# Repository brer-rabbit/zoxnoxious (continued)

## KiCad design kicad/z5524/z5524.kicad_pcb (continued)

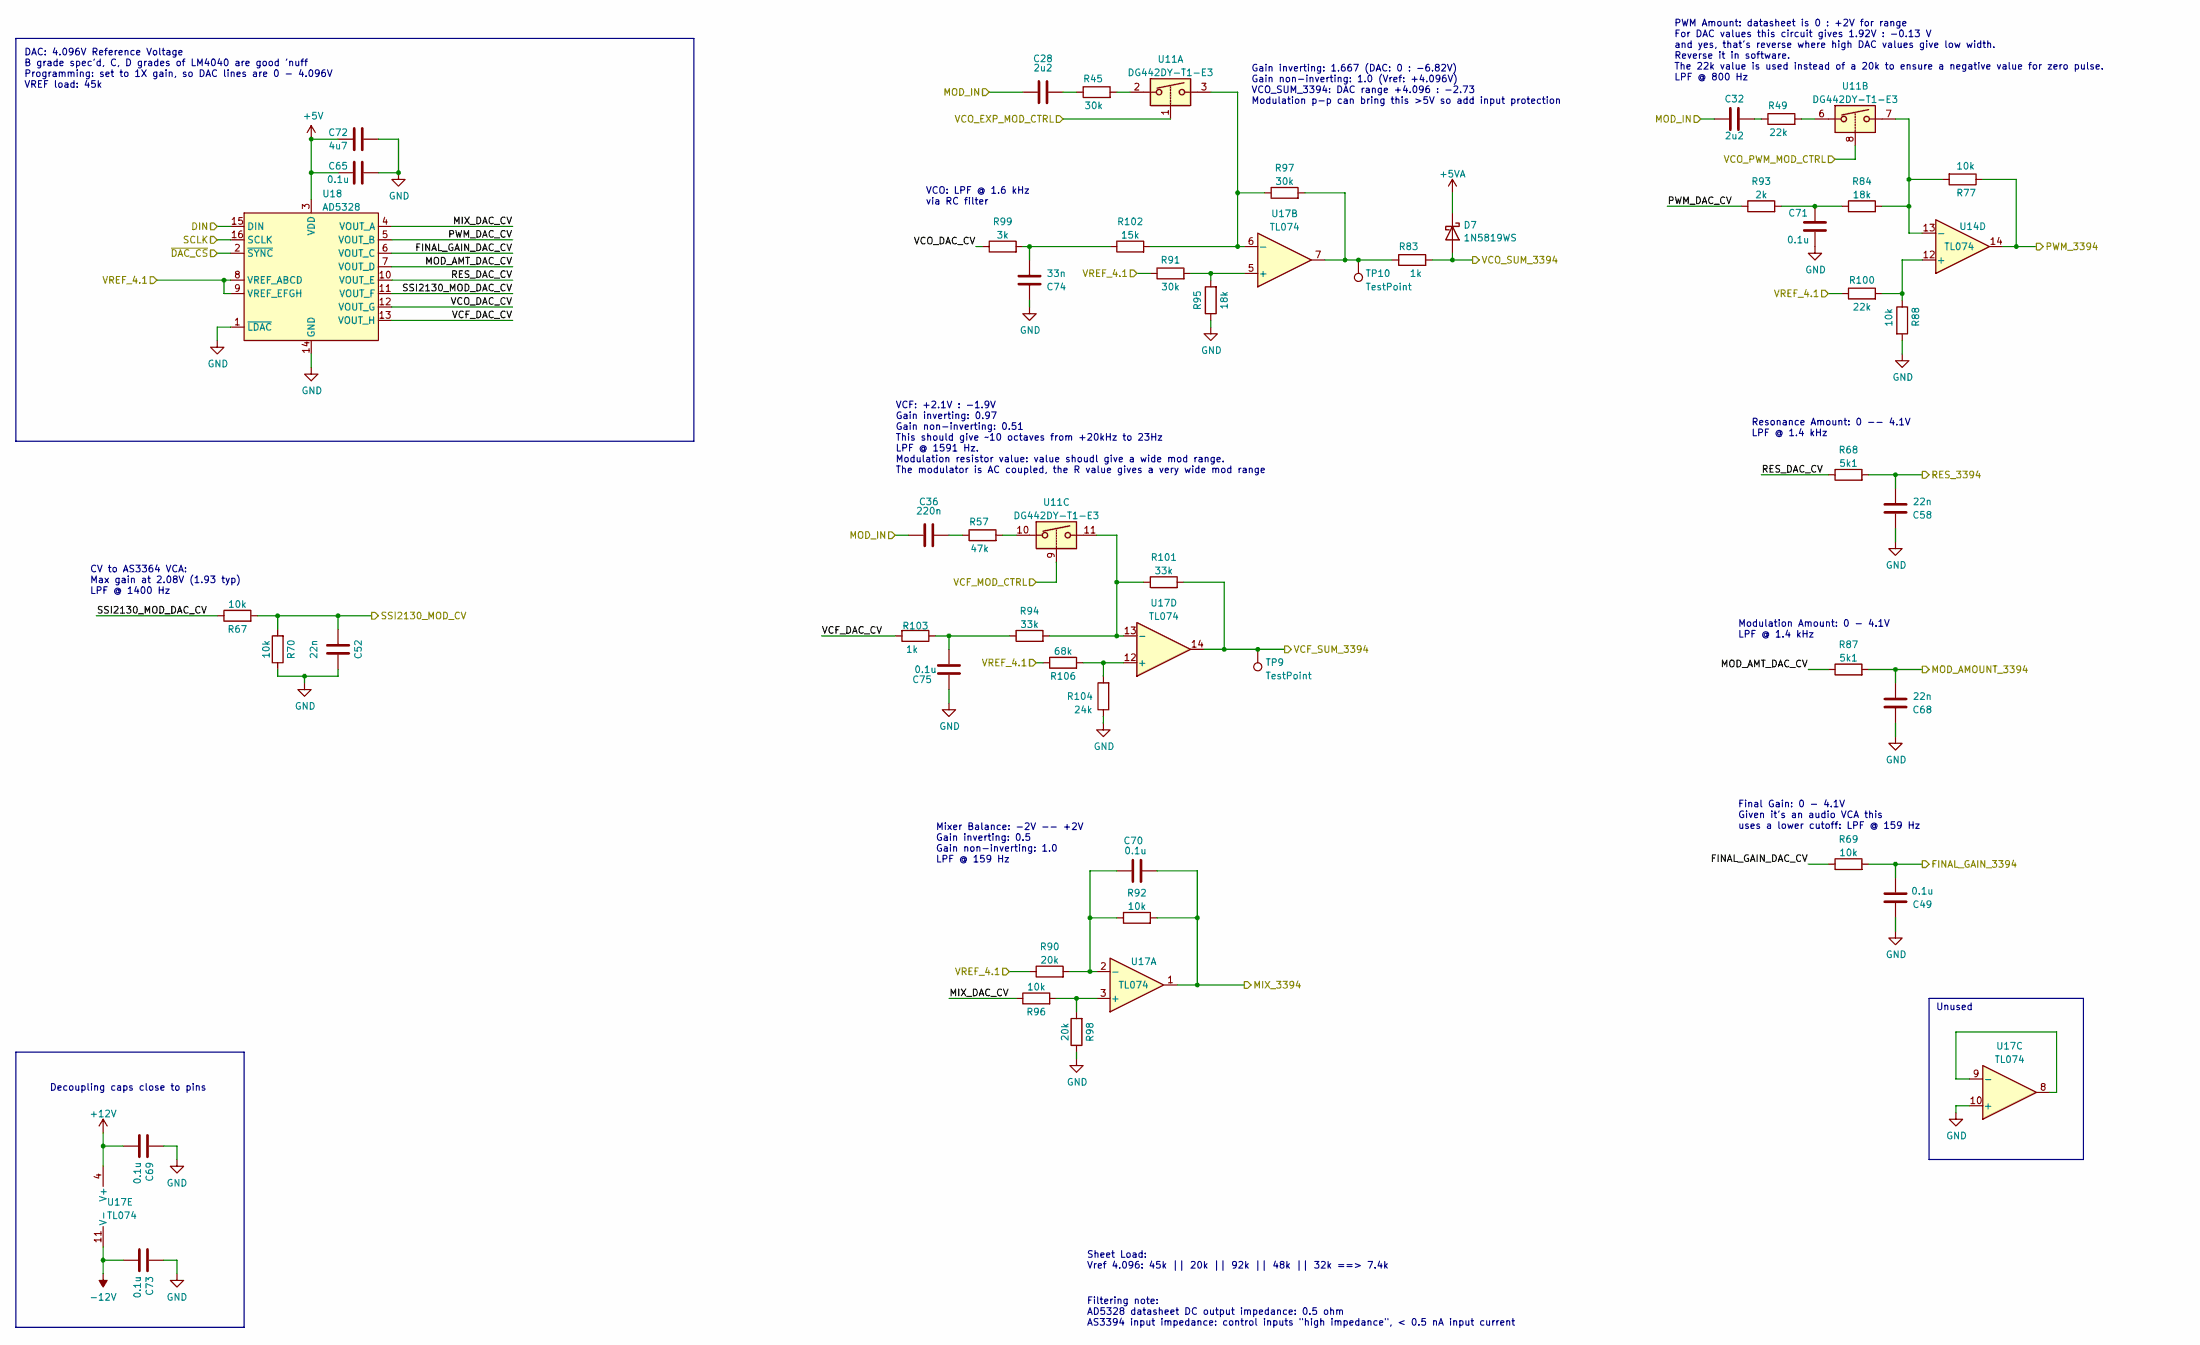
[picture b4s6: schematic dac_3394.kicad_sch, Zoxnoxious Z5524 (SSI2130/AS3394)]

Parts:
C28, C32: 2u2; C_0603_1608Metric; LCSC C23630
C36: 220n; C_0603_1608Metric; LCSC C21120
C49, C65, C69, C70, C71, C73, C75: 0.1u; C_0603_1608Metric; LCSC C14663
C52, C58, C68: 22n; C_0603_1608Metric; LCSC C21122
C72: 4u7; C_0603_1608Metric; LCSC C19666
C74: 33n; C_0603_1608Metric; LCSC C21117
D7: 1N5819WS; D_SOD-323; LCSC C191023
R45, R91, R97: 30k; R_0603_1608Metric; LCSC C22984
R49, R100: 22k; R_0603_1608Metric; LCSC C31850
R57: 47k; R_0603_1608Metric; LCSC C25819
R67, R69, R70, R77, R88, R92, R96: 10k; R_0603_1608Metric; LCSC C25804
R68, R87: 5k1; R_0603_1608Metric; LCSC C23186
R83, R103: 1k; R_0603_1608Metric; LCSC C21190
R84, R95: 18k; R_0603_1608Metric; LCSC C25810
R90, R98: 20k; R_0603_1608Metric; LCSC C4184
R93: 2k; R_0603_1608Metric; LCSC C22975
R94, R101: 33k; R_0603_1608Metric; LCSC C4216
R99: 3k; R_0603_1608Metric; LCSC C4211
R102: 15k; R_0603_1608Metric; LCSC C22809
R104: 24k; R_0603_1608Metric; LCSC C23352
R106: 68k; R_0603_1608Metric; LCSC C23231
TP9, TP10: TestPoint; TestPoint_Pad_1.5x1.5mm
U11: DG442DY-T1-E3; SOIC-16_3.9x9.9mm_P1.27mm; LCSC C2673321
U14, U17: TL074; TSSOP-14_4.4x5mm_P0.65mm; LCSC C96507
U18: AD5328; TSSOP-16_4.4x5mm_P0.65mm; LCSC C29162

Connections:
+5V: C65.1, C72.1, U18.3 (VDD); also elsewhere on the board
+5VA: D7.1 (K); also elsewhere on the board
+12V: C69.2, U17.4 (V+); also elsewhere on the board
-12V: C73.2, U17.11 (V-); also elsewhere on the board
/AS3394/FINAL_GAIN_CV: C49.1, R69.2; also elsewhere on the board
/AS3394/MIX_CV: C70.2, R92.2, U17.1; also elsewhere on the board
/AS3394/MOD_AMOUNT_CV: C68.1, R87.2; also elsewhere on the board
/AS3394/PWM_SUM: R77.1, U14.14; also elsewhere on the board
/AS3394/RES_CV: C58.1, R68.2; also elsewhere on the board
/AS3394/VCF_SUM: R101.2, TP9.1, U17.14; also elsewhere on the board
/AS3394/VCO_SUM: D7.2 (A), R83.2; also elsewhere on the board
/DAC 3394/FINAL_GAIN_DAC_CV: R69.1, U18.6 (VOUT_C)
/DAC 3394/MIX_DAC_CV: R96.1, U18.4 (VOUT_A)
/DAC 3394/MOD_AMT_DAC_CV: R87.1, U18.7 (VOUT_D)
/DAC 3394/PWM_DAC_CV: R93.1, U18.5 (VOUT_B)
/DAC 3394/RES_DAC_CV: R68.1, U18.10 (VOUT_E)
/DAC 3394/SSI2130_MOD_DAC_CV: R67.1, U18.11 (VOUT_F)
/DAC 3394/VCF_DAC_CV: R103.2, U18.13 (VOUT_H)
/DAC 3394/VCO_DAC_CV: R99.1, U18.12 (VOUT_G)
/PWM3394_MOD_CTRL: U11.8; also elsewhere on the board
/SPI_CLK: U18.16 (SCLK); also elsewhere on the board
/SPI_CS0: U18.2 (~SYNC); also elsewhere on the board
/SPI_MOSI: U18.15 (DIN); also elsewhere on the board
/SSI2130_MOD: C28.1, C32.1, C36.1; also elsewhere on the board
/SSI2130_MOD_CV: C52.2, R67.2, R70.2; also elsewhere on the board
/VCF3394_MOD_CTRL: U11.9; also elsewhere on the board
/VCO3394_EXP_MOD_CTRL: U11.1; also elsewhere on the board
/VREF_4.096: R90.1, R91.1, R100.1, R106.1, U18.8 (VREF_ABCD), U18.9 (VREF_EFGH); also elsewhere on the board
GND: C49.2, C52.1, C58.2, C65.2, C68.2, C69.1, C71.1, C72.2, C73.1, C74.2, C75.2, R70.1, R88.2, R95.1, R98.1, R104.1, U17.10 (+), U18.1 (~LDAC), U18.14 (GND); also elsewhere on the board
unnamed: C28.2, R45.1
unnamed: C32.2, R49.1
unnamed: C36.2, R57.1
unnamed: C71.2, R84.1, R93.2
unnamed: C74.1, R99.2, R102.1
unnamed: C75.1, R94.1, R103.1
unnamed: R45.2, U11.2
unnamed: R49.2, U11.6
unnamed: R57.2, U11.10
unnamed: R83.1, R97.2, TP10.1, U17.7
unnamed: R88.1, R100.2, U14.12 (+)
unnamed: R77.2, R84.2, U11.7, U14.13 (-)
unnamed: R96.2, R98.2, U17.3 (+)
unnamed: C70.1, R90.2, R92.1, U17.2 (-)
unnamed: R91.2, R95.2, U17.5 (+)
unnamed: R97.1, R102.2, U11.3, U17.6 (-)
unnamed: U17.8, U17.9 (-)
unnamed: R104.2, R106.2, U17.12 (+)
unnamed: R94.2, R101.1, U11.11, U17.13 (-)

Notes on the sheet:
PWM Amount: datasheet is 0 : +2V for range For DAC values this circuit gives 1.92V : -0.13 V and yes, that's reverse where high DAC values give low width. Reverse it in software. The 22k value is used instead of a 20k to ensure a negative value for zero pulse. LPF @ 800 Hz
VCO: LPF @ 1.6 kHz via RC filter
VCF: +2.1V : -1.9V Gain inverting: 0.97 Gain non-inverting: 0.51 This should give ~10 octaves from +20kHz to 23Hz LPF @ 1591 Hz. Modulation resistor value: value shoudl give a wide mod range. The modulator is AC coupled, the R value gives a very wide mod range
Resonance Amount: 0 -- 4.1V LPF @ 1.4 kHz
Unused
Sheet Load: Vref 4.096: 45k || 20k || 92k || 48k || 32k ==> 7.4k
Mixer Balance: -2V -- +2V Gain inverting: 0.5 Gain non-inverting: 1.0 LPF @ 159 Hz
Modulation Amount: 0 - 4.1V LPF @ 1.4 kHz
Filtering note: AD5328 datasheet DC output impedance: 0.5 ohm AS3394 input impedance: control inputs "high impedance", < 0.5 nA input current
Final Gain: 0 - 4.1V Given it's an audio VCA this uses a lower cutoff: LPF @ 159 Hz
DAC: 4.096V Reference Voltage B grade spec'd, C, D grades of LM4040 are good 'nuff Programming: set to 1X gain, so DAC lines are 0 - 4.096V VREF load: 45k
CV to AS3364 VCA: Max gain at 2.08V (1.93 typ) LPF @ 1400 Hz
Decoupling caps close to pins
Gain inverting: 1.667 (DAC: 0 : -6.82V) Gain non-inverting: 1.0 (Vref: +4.096V) VCO_SUM_3394: DAC range +4.096 : -2.73 Modulation p-p can bring this >5V so add input protection

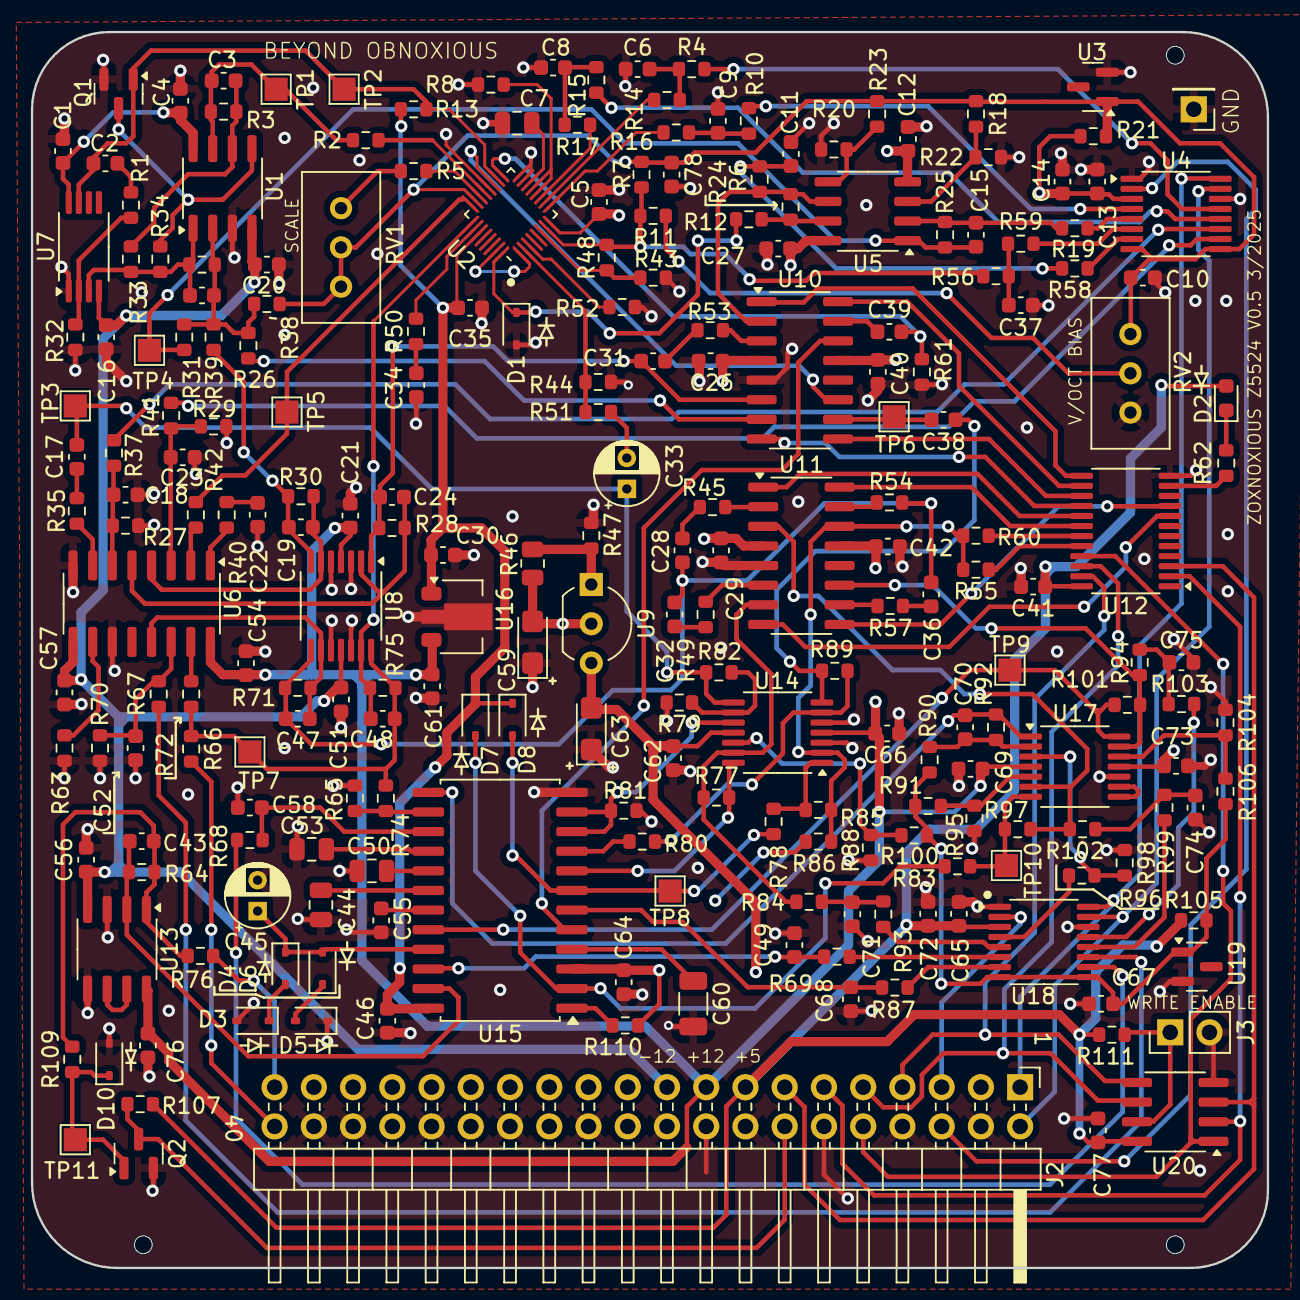
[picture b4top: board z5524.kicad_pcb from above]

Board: 4 copper layers, 80.0 x 80.0 mm, 233 parts (0 on the bottom side), 164 nets.

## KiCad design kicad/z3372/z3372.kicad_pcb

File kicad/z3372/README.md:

# Z3372 Voltage Controlled Filter & Noise Source

The Z3372 Analog Signal Processor utilized Alfa Rpar's AS3372 VCF/VCA.  It also contains a white noise source which can be run through the filter.  Some interseting modulation options are present, along with a stereo output.

# Block Diagram

# Resources

[Datasheet](datasheet_z3372.pdf)

[KiCanvas](https://kicanvas.org/?github=https%3A%2F%2Fgithub.com%2Fbrer-rabbit%2Fzoxnoxious%2Ftree%2Fmain%2Fkicad%2Fz3372)

# Demo

(old!) YouTube Demo

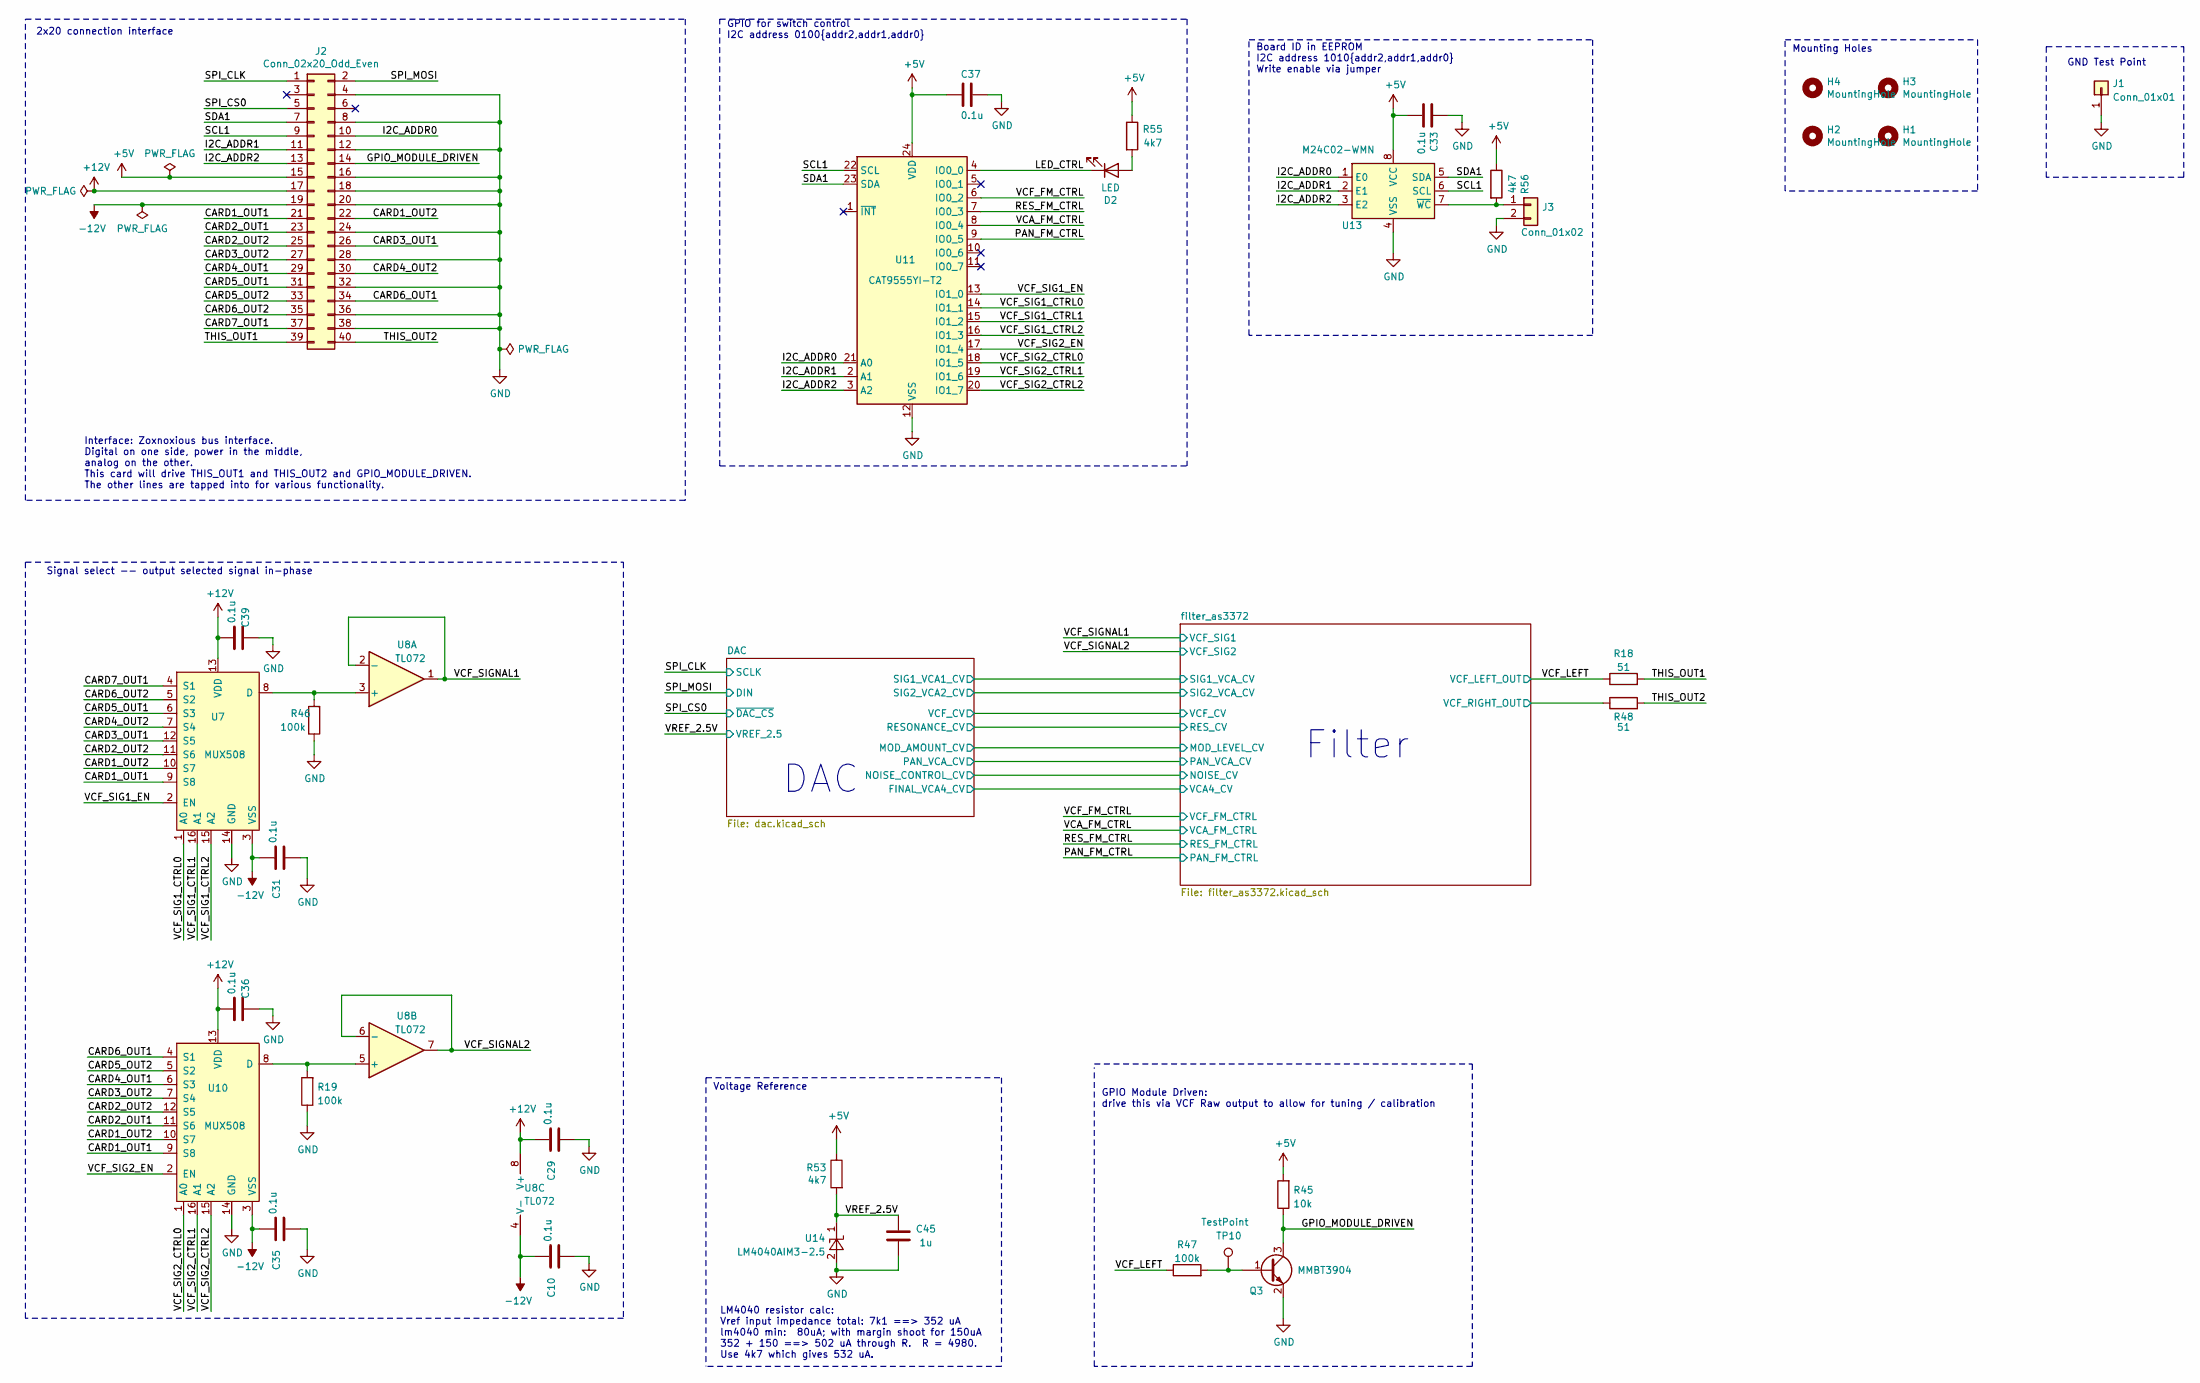
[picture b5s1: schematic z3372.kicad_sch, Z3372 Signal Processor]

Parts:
C10, C29, C31, C33, C35, C36, C37, C39: 0.1u; C_0603_1608Metric; LCSC C14663
C45: 1u; C_0805_2012Metric; LCSC C28323
D2: LED; LED_0603_1608Metric; LCSC C2286
H1, H2, H3, H4: MountingHole; MountingHole_3.2mm_M3
J1: Conn_01x01; PinHeader_1x01_P2.54mm_Vertical
J2: Conn_02x20_Odd_Even; PinHeader_2x20_P2.54mm_Horizontal
J3: Conn_01x02; PinHeader_1x02_P2.54mm_Vertical
Q3: MMBT3904; SOT-23; LCSC C20526
R18, R48: 51; R_0603_1608Metric; LCSC C23197
R19, R46, R47: 100k; R_0603_1608Metric; LCSC C25803
R45: 10k; R_0603_1608Metric; LCSC C25804
R53, R55, R56: 4k7; R_0603_1608Metric; LCSC C23162
TP10: TestPoint; TestPoint_Pad_2.0x2.0mm
U7, U10: MUX508; SOIC-16_3.9x9.9mm_P1.27mm; LCSC C2673104
U8: TL072; SOIC-8_3.9x4.9mm_P1.27mm; LCSC C6961
U11: CAT9555YI-T2; TSSOP-24_4.4x7.8mm_P0.65mm; LCSC C83265
U13: M24C02-WMN; SOIC-8_3.9x4.9mm_P1.27mm; LCSC C7562
U14: LM4040AIM3-2.5; SOT-23; LCSC C460725

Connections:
+5V: C33.2, C37.2, J2.15, R45.2, R53.1, R55.1, R56.1, U11.24 (VDD), U13.8 (VCC); also elsewhere on the board
+12V: C29.2, C36.2, C39.2, J2.17, U7.13 (VDD), U8.8 (V+), U10.13 (VDD); also elsewhere on the board
-12V: C10.2, C31.2, C35.2, J2.19, U7.3 (VSS), U8.4 (V-), U10.3 (VSS); also elsewhere on the board
/CARD1_OUT1: J2.21, U7.9 (S8), U10.9 (S8)
/CARD1_OUT2: J2.22, U7.10 (S7), U10.10 (S7)
/CARD2_OUT1: J2.23, U10.11 (S6)
/CARD2_OUT2: J2.25, U7.11 (S6), U10.12 (S5)
/CARD3_OUT1: J2.26, U7.12 (S5)
/CARD3_OUT2: J2.27, U10.7 (S4)
/CARD4_OUT1: J2.29, U10.6 (S3)
/CARD4_OUT2: J2.30, U7.7 (S4)
/CARD5_OUT1: J2.31, U7.6 (S3)
/CARD5_OUT2: J2.33, U10.5 (S2)
/CARD6_OUT1: J2.34, U10.4 (S1)
/CARD6_OUT2: J2.35, U7.5 (S2)
/CARD7_OUT1: J2.37, U7.4 (S1)
/GPIO_MODULE_DRIVEN: J2.14, Q3.3 (C), R45.1
/I2C_ADDR0: J2.10, U11.21 (A0), U13.1 (E0)
/I2C_ADDR1: J2.11, U11.2 (A1), U13.2 (E1)
/I2C_ADDR2: J2.13, U11.3 (A2), U13.3 (E2)
/LED_CTRL: D2.1 (K), U11.4 (IO0_0)
/PAN_FM_CTRL: U11.9 (IO0_5); also elsewhere on the board
/RES_FM_CTRL: U11.7 (IO0_3); also elsewhere on the board
/SCL1: J2.9, U11.22 (SCL), U13.6 (SCL)
/SDA1: J2.7, U11.23 (SDA), U13.5 (SDA)
/SPI_CLK: J2.1; also elsewhere on the board
/SPI_CS0: J2.5; also elsewhere on the board
/SPI_MOSI: J2.2; also elsewhere on the board
/THIS_OUT1: J2.39, R18.2
/THIS_OUT2: J2.40, R48.2
/VCA_FM_CTRL: U11.8 (IO0_4); also elsewhere on the board
/VCF_FM_CTRL: U11.6 (IO0_2); also elsewhere on the board
/VCF_LEFT: R18.1, R47.1; also elsewhere on the board
/VCF_SIG1_CTRL0: U7.1 (A0), U11.14 (IO1_1)
/VCF_SIG1_CTRL1: U7.16 (A1), U11.15 (IO1_2)
/VCF_SIG1_CTRL2: U7.15 (A2), U11.16 (IO1_3)
/VCF_SIG1_EN: U7.2 (EN), U11.13 (IO1_0)
/VCF_SIG2_CTRL0: U10.1 (A0), U11.18 (IO1_5)
/VCF_SIG2_CTRL1: U10.16 (A1), U11.19 (IO1_6)
/VCF_SIG2_CTRL2: U10.15 (A2), U11.20 (IO1_7)
/VCF_SIG2_EN: U10.2 (EN), U11.17 (IO1_4)
/VCF_SIGNAL1: U8.1, U8.2 (-); also elsewhere on the board
/VCF_SIGNAL2: U8.6 (-), U8.7; also elsewhere on the board
/VREF_2.5V: C45.1, R53.2, U14.1 (K); also elsewhere on the board
/filter_as3372/VCF_RIGHT_OUT: R48.1; also elsewhere on the board
GND: C10.1, C29.1, C31.1, C33.1, C35.1, C36.1, C37.1, C39.1, C45.2, J1.1, J2.4, J2.8, J2.12, J2.16, J2.18, J2.20, J2.24, J2.28, J2.32, J2.36, J2.38, J3.2, Q3.2 (E), R19.1, R46.1, U7.14 (GND), U10.14 (GND), U11.12 (VSS), U13.4 (VSS), U14.2 (A); also elsewhere on the board
unnamed: D2.2 (A), R55.2
unnamed: J3.1, R56.2, U13.7 (~WC)
unnamed: Q3.1 (B), R47.2, TP10.1
unnamed: R46.2, U7.8 (D), U8.3 (+)
unnamed: R19.2, U8.5 (+), U10.8 (D)

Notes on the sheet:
Filter
Signal select -- output selected signal in-phase
Voltage Reference
2x20 connection interface
GPIO Module Driven: drive this via VCF Raw output to allow for tuning / calibration
GPIO for switch control I2C address 0100{addr2,addr1,addr0}
Mounting Holes
LM4040 resistor calc: Vref input impedance total: 7k1 ==> 352 uA lm4040 min: 80uA; with margin shoot for 150uA 352 + 150 ==> 502 uA through R. R = 4980. Use 4k7 which gives 532 uA.
GND Test Point
Board ID in EEPROM I2C address 1010{addr2,addr1,addr0} Write enable via jumper
Interface: Zoxnoxious bus interface. Digital on one side, power in the middle, analog on the other. This card will drive THIS_OUT1 and THIS_OUT2 and GPIO_MODULE_DRIVEN. The other lines are tapped into for various functionality.
DAC

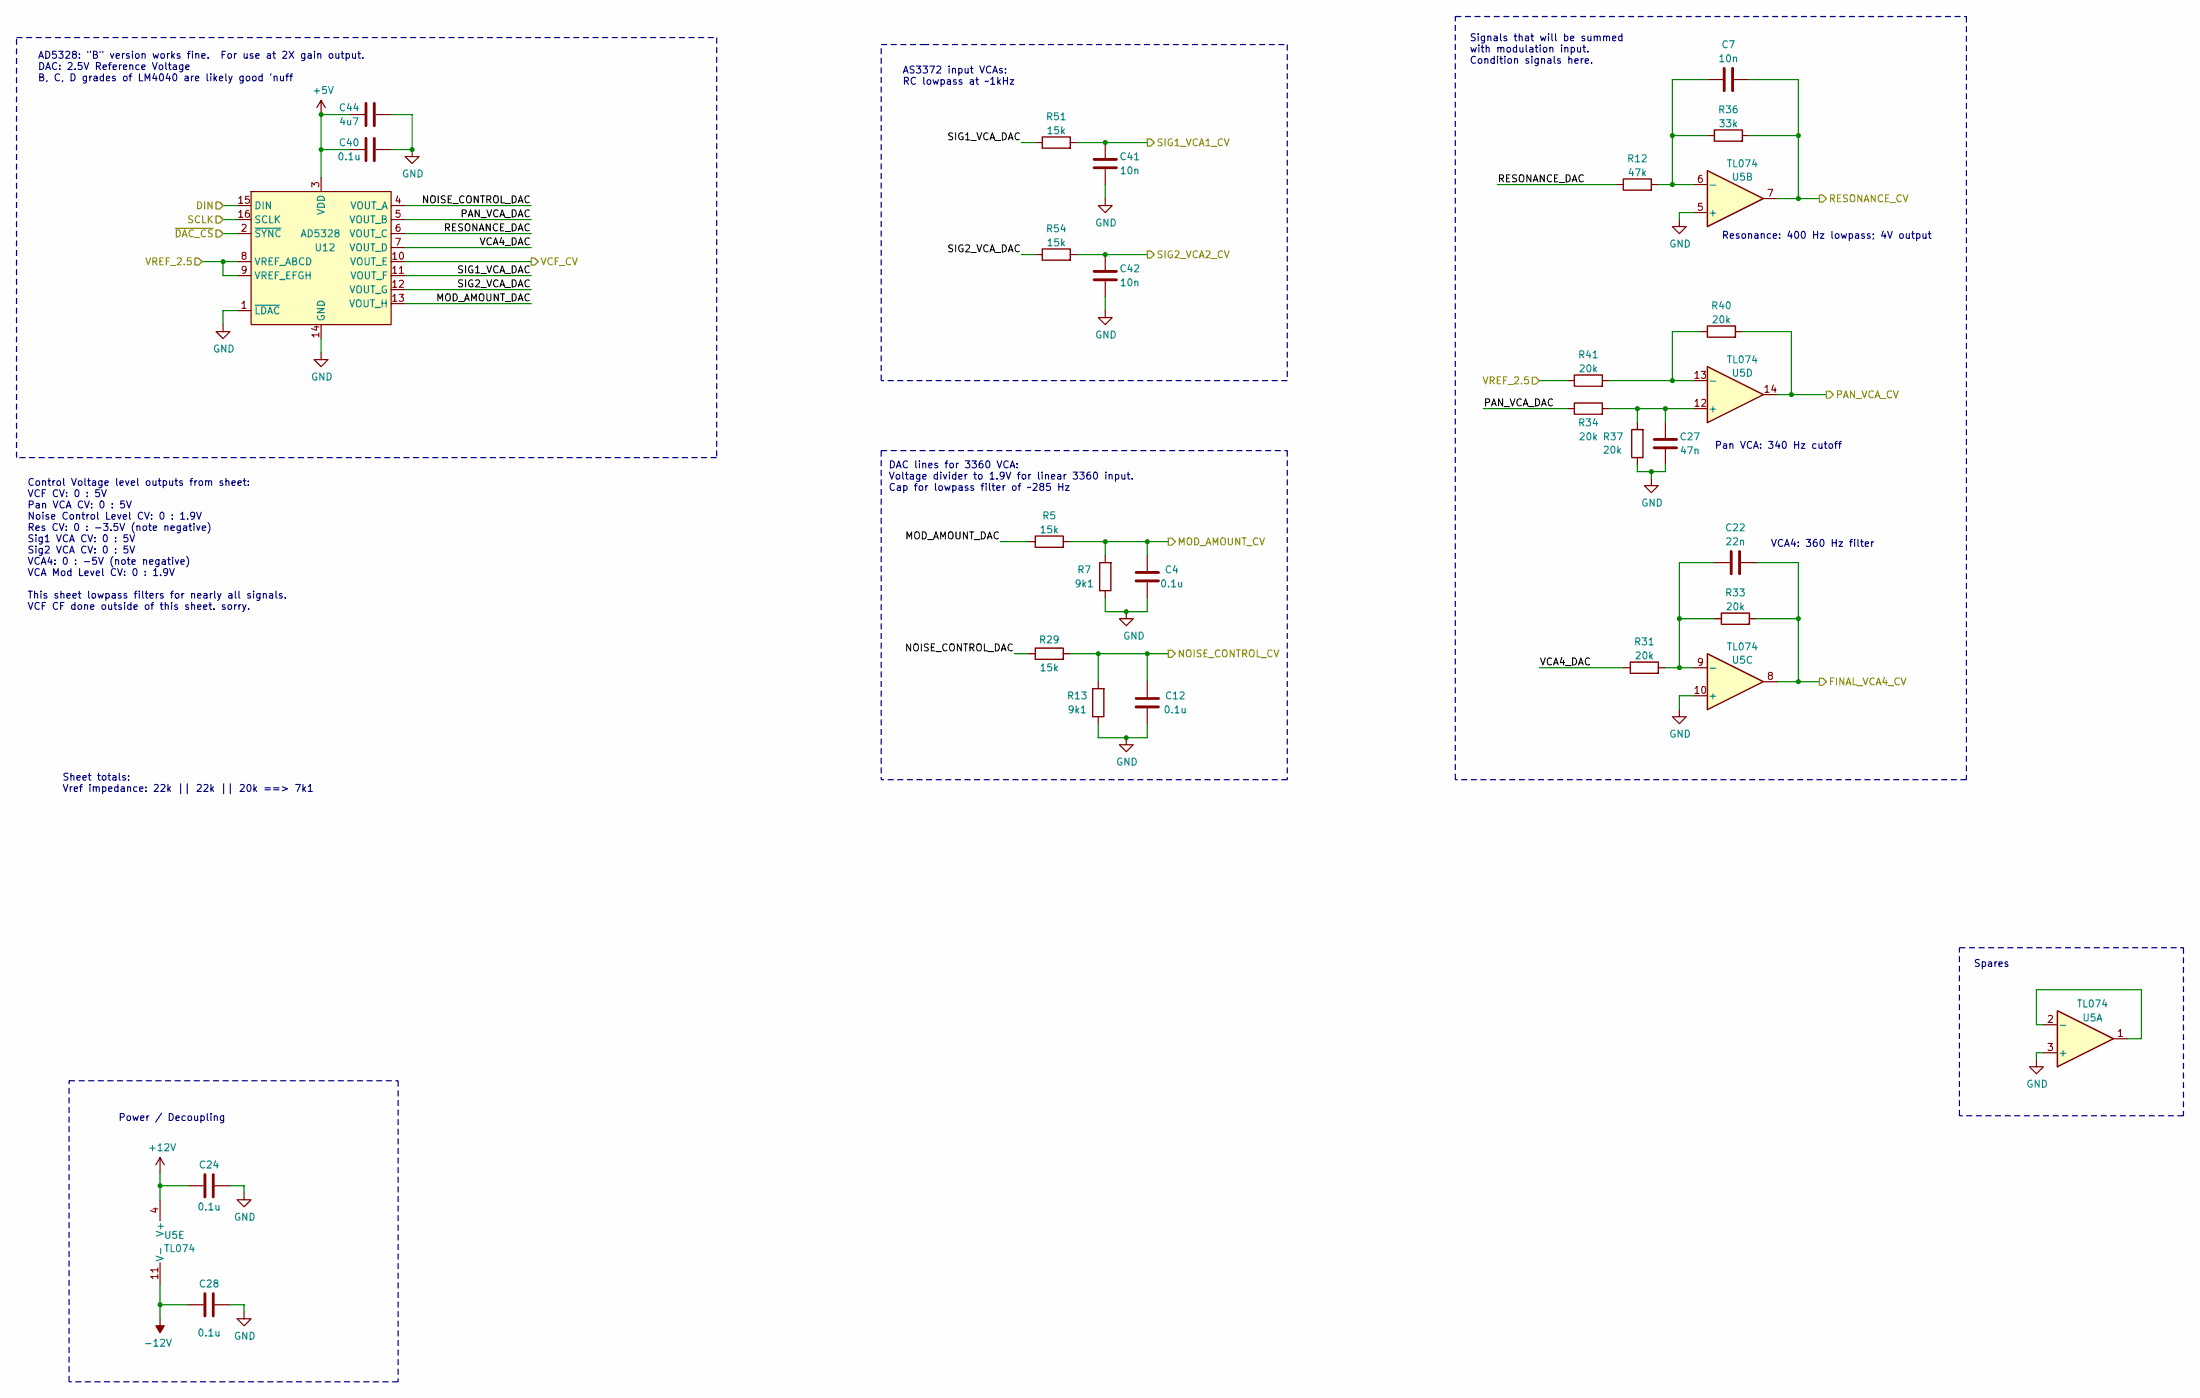
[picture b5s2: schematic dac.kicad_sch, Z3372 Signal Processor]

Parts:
C4, C12, C24, C28, C40: 0.1u; C_0603_1608Metric; LCSC C14663
C7, C41, C42: 10n; C_0603_1608Metric; LCSC C57112
C22: 22n; C_0603_1608Metric; LCSC C21122
C27: 47n; C_0603_1608Metric; LCSC C1622
C44: 4u7; C_0805_2012Metric; LCSC C1779
R5, R29, R51, R54: 15k; R_0603_1608Metric; LCSC C22809
R7, R13: 9k1; R_0603_1608Metric; LCSC C23260
R12: 47k; R_0603_1608Metric; LCSC C25819
R31, R33, R34, R37, R40, R41: 20k; R_0603_1608Metric; LCSC C4184
R36: 33k; R_0603_1608Metric; LCSC C4216
U5: TL074; TSSOP-14_4.4x5mm_P0.65mm; LCSC C96507
U12: AD5328; TSSOP-16_4.4x5mm_P0.65mm; LCSC C29162

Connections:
+5V: C40.1, C44.1, U12.3 (VDD); also elsewhere on the board
+12V: C24.1, U5.4 (V+); also elsewhere on the board
-12V: C28.1, U5.11 (V-); also elsewhere on the board
/DAC/FINAL_VCA4_CV: C22.2, R33.2, U5.8; also elsewhere on the board
/DAC/MOD_AMOUNT_CV: C4.1, R5.2, R7.2; also elsewhere on the board
/DAC/MOD_AMOUNT_DAC: R5.1, U12.13 (VOUT_H)
/DAC/NOISE_CONTROL_CV: C12.1, R13.2, R29.2; also elsewhere on the board
/DAC/NOISE_CONTROL_DAC: R29.1, U12.4 (VOUT_A)
/DAC/PAN_VCA_CV: R40.2, U5.14; also elsewhere on the board
/DAC/PAN_VCA_DAC: R34.1, U12.5 (VOUT_B)
/DAC/RESONANCE_CV: C7.2, R36.2, U5.7; also elsewhere on the board
/DAC/RESONANCE_DAC: R12.1, U12.6 (VOUT_C)
/DAC/SIG1_VCA1_CV: C41.1, R51.2; also elsewhere on the board
/DAC/SIG1_VCA_DAC: R51.1, U12.11 (VOUT_F)
/DAC/SIG2_VCA2_CV: C42.1, R54.2; also elsewhere on the board
/DAC/SIG2_VCA_DAC: R54.1, U12.12 (VOUT_G)
/DAC/VCA4_DAC: R31.1, U12.7 (VOUT_D)
/DAC/VCF_CV: U12.10 (VOUT_E); also elsewhere on the board
/SPI_CLK: U12.16 (SCLK); also elsewhere on the board
/SPI_CS0: U12.2 (~SYNC); also elsewhere on the board
/SPI_MOSI: U12.15 (DIN); also elsewhere on the board
/VREF_2.5V: R41.1, U12.8 (VREF_ABCD), U12.9 (VREF_EFGH); also elsewhere on the board
GND: C4.2, C12.2, C24.2, C27.2, C28.2, C40.2, C41.2, C42.2, C44.2, R7.1, R13.1, R37.1, U5.3 (+), U5.5 (+), U5.10 (+), U12.1 (~LDAC), U12.14 (GND); also elsewhere on the board
unnamed: U5.1, U5.2 (-)
unnamed: C7.1, R12.2, R36.1, U5.6 (-)
unnamed: C22.1, R31.2, R33.1, U5.9 (-)
unnamed: C27.1, R34.2, R37.2, U5.12 (+)
unnamed: R40.1, R41.2, U5.13 (-)

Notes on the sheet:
AS3372 input VCAs: RC lowpass at ~1kHz
Power / Decoupling
Spares
VCA4: 360 Hz filter
DAC lines for 3360 VCA: Voltage divider to 1.9V for linear 3360 input. Cap for lowpass filter of ~285 Hz
Signals that will be summed with modulation input. Condition signals here.
Resonance: 400 Hz lowpass; 4V output
Sheet totals: Vref impedance: 22k || 22k || 20k ==> 7k1
Control Voltage level outputs from sheet: VCF CV: 0 : 5V Pan VCA CV: 0 : 5V Noise Control Level CV: 0 : 1.9V Res CV: 0 : -3.5V (note negative) Sig1 VCA CV: 0 : 5V Sig2 VCA CV: 0 : 5V VCA4: 0 : -5V (note negative) VCA Mod Level CV: 0 : 1.9V This sheet lowpass filters for nearly all signals. VCF CF d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
Pan VCA: 340 Hz cutoff
AD5328: "B" version works fine. For use at 2X gain output. DAC: 2.5V Reference Voltage B, C, D grades of LM4040 are likely good 'nuff
